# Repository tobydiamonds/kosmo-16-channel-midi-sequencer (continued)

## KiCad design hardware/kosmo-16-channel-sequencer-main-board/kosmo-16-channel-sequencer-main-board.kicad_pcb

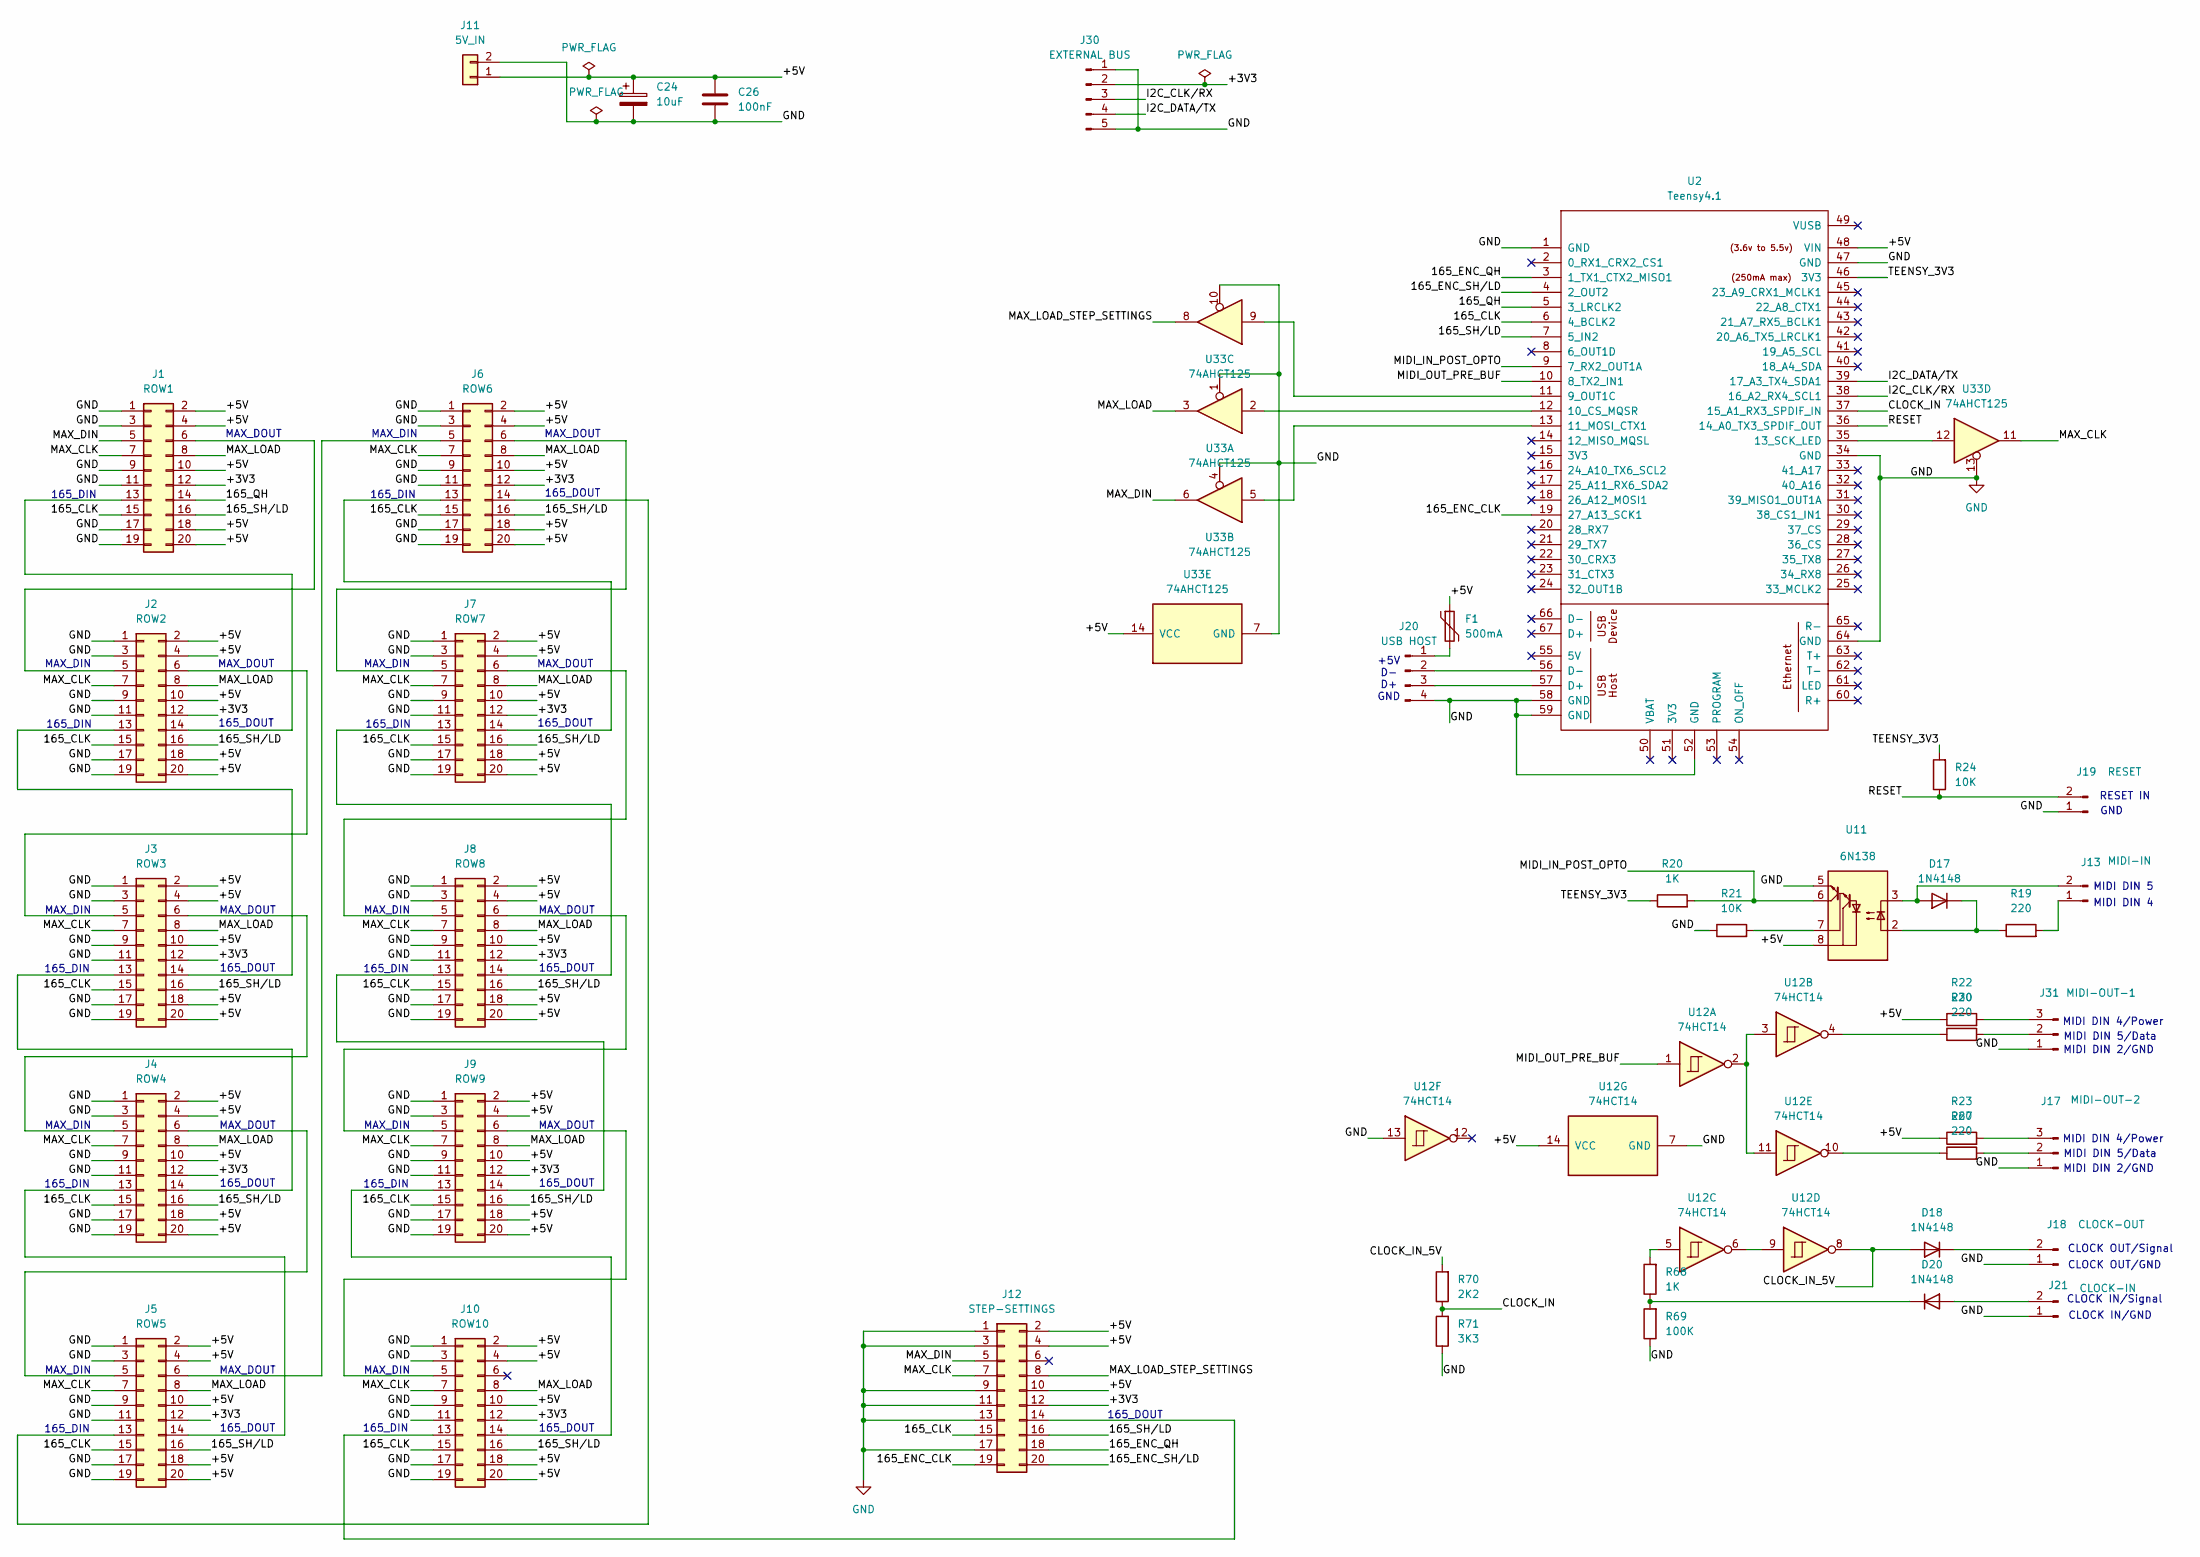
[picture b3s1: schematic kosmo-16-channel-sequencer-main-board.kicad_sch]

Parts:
C24: 10uF; CP_Radial_D6.3mm_P2.50mm
C26: 100nF; C_Disc_D5.0mm_W2.5mm_P5.00mm
D17, D18, D20: 1N4148; D_DO-35_SOD27_P7.62mm_Horizontal
F1: 500mA; Fuse_Bourns_MF-RHT050
J1: ROW1; PinHeader_2x10_P2.54mm_Vertical
J2: ROW2; PinHeader_2x10_P2.54mm_Vertical
J3: ROW3; PinHeader_2x10_P2.54mm_Vertical
J4: ROW4; PinHeader_2x10_P2.54mm_Vertical
J5: ROW5; PinHeader_2x10_P2.54mm_Vertical
J6: ROW6; PinHeader_2x10_P2.54mm_Vertical
J7: ROW7; PinHeader_2x10_P2.54mm_Vertical
J8: ROW8; PinHeader_2x10_P2.54mm_Vertical
J9: ROW9; PinHeader_2x10_P2.54mm_Vertical
J10: ROW10; PinHeader_2x10_P2.54mm_Vertical
J11: 5V_IN; TerminalBlock_Xinya_XY308-2.54-2P_1x02_P2.54mm_Horizontal
J12: STEP-SETTINGS; PinHeader_2x10_P2.54mm_Vertical
J13: MIDI-IN; PinHeader_1x02_P2.54mm_Vertical
J17: MIDI-OUT-2; PinHeader_1x03_P2.54mm_Vertical
J18: CLOCK-OUT; PinHeader_1x02_P2.54mm_Vertical
J19: RESET; PinHeader_1x02_P2.54mm_Vertical
J20: USB HOST; PinHeader_1x04_P2.54mm_Vertical
J21: CLOCK-IN; PinHeader_1x02_P2.54mm_Vertical
J30: EXTERNAL BUS; PinHeader_1x05_P2.54mm_Vertical
J31: MIDI-OUT-1; PinHeader_1x03_P2.54mm_Vertical
R19, R22, R23, R30, R67: 220; R_Axial_DIN0207_L6.3mm_D2.5mm_P7.62mm_Horizontal
R20, R68: 1K; R_Axial_DIN0207_L6.3mm_D2.5mm_P7.62mm_Horizontal
R21, R24: 10K; R_Axial_DIN0207_L6.3mm_D2.5mm_P7.62mm_Horizontal
R69: 100K; R_Axial_DIN0207_L6.3mm_D2.5mm_P7.62mm_Horizontal
R70: 2K2; R_Axial_DIN0207_L6.3mm_D2.5mm_P7.62mm_Horizontal
R71: 3K3; R_Axial_DIN0207_L6.3mm_D2.5mm_P7.62mm_Horizontal
U2: Teensy4.1; Teensy41
U11: 6N138; DIP-8_W7.62mm
U12: 74HCT14; DIP-14_W7.62mm
U33: 74AHCT125; DIP-14_W7.62mm

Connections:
/165_CLK: J1.15, J2.15, J3.15, J4.15, J5.15, J6.15, J7.15, J8.15, J9.15, J10.15, J12.15, U2.6 (4_BCLK2)
/165_ENC_CLK: J12.19, U2.19 (27_A13_SCK1)
/165_ENC_QH: J12.18, U2.3 (1_TX1_CTX2_MISO1)
/165_ENC_SH/LD: J12.20, U2.4 (2_OUT2)
/165_QH: J1.14, U2.5 (3_LRCLK2)
/165_SH/LD: J1.16, J2.16, J3.16, J4.16, J5.16, J6.16, J7.16, J8.16, J9.16, J10.16, J12.16, U2.7 (5_IN2)
/+3V3: J1.12, J2.12, J3.12, J4.12, J5.12, J6.12, J7.12, J8.12, J9.12, J10.12, J12.12, J30.2
/+5V: C24.1, C26.1, F1.1, J1.2, J1.4, J1.10, J1.18, J1.20, J2.2, J2.4, J2.10, J2.18, J2.20, J3.2, J3.4, J3.10, J3.18, J3.20, J4.2, J4.4, J4.10, J4.18, J4.20, J5.2, J5.4, J5.10, J5.18, J5.20, J6.2, J6.4, J6.10, J6.18, J6.20, J7.2, J7.4, J7.10, J7.18, J7.20, J8.2, J8.4, J8.10, J8.18, J8.20, J9.2, J9.4, J9.10, J9.18, J9.20, J10.2, J10.4, J10.10, J10.18, J10.20, J11.1, J12.2, J12.4, J12.10, R22.1, R23.1, U2.48 (VIN), U11.8 (VCC), U12.14 (VCC), U33.14 (VCC)
/CLOCK_IN: R70.1, R71.2, U2.37 (15_A1_RX3_SPDIF_IN)
/CLOCK_IN_5V: D18.2 (A), R70.2, U12.8
/I2C_CLK/RX: J30.3, U2.38 (16_A2_RX4_SCL1)
/I2C_DATA/TX: J30.4, U2.39 (17_A3_TX4_SDA1)
/MAX_CLK: J1.7, J2.7, J3.7, J4.7, J5.7, J6.7, J7.7, J8.7, J9.7, J10.7, J12.7, U33.11
/MAX_DIN: J1.5, J12.5, U33.6
/MAX_LOAD: J1.8, J2.8, J3.8, J4.8, J5.8, J6.8, J7.8, J8.8, J9.8, J10.8, U33.3
/MAX_LOAD_STEP_SETTINGS: J12.8, U33.8
/MIDI_IN_POST_OPTO: R20.2, U2.9 (7_RX2_OUT1A), U11.6 (VO2)
/MIDI_OUT_PRE_BUF: U2.10 (8_TX2_IN1), U12.1
/RESET: J19.2, R24.1, U2.36 (14_A0_TX3_SPDIF_OUT)
/TEENSY_3V3: R20.1, R24.2, U2.46 (3V3)
GND: C24.2, C26.2, J1.1, J1.3, J1.9, J1.11, J1.17, J1.19, J2.1, J2.3, J2.9, J2.11, J2.17, J2.19, J3.1, J3.3, J3.9, J3.11, J3.17, J3.19, J4.1, J4.3, J4.9, J4.11, J4.17, J4.19, J5.1, J5.3, J5.9, J5.11, J5.17, J5.19, J6.1, J6.3, J6.9, J6.11, J6.17, J6.19, J7.1, J7.3, J7.9, J7.11, J7.17, J7.19, J8.1, J8.3, J8.9, J8.11, J8.17, J8.19, J9.1, J9.3, J9.9, J9.11, J9.17, J9.19, J10.1, J10.3, J10.9, J10.11, J10.17, J10.19, J11.2, J12.1, J12.3, J12.9, J12.11, J12.13, J12.17, J17.1, J18.1, J19.1, J20.4, J21.1, J30.1, J30.5, J31.1, R21.1, R69.1, R71.1, U2.1 (GND), U2.34 (GND), U2.47 (GND), U2.52 (GND), U2.58 (GND), U2.59 (GND), U2.64 (GND), U11.5 (GND), U12.7 (GND), U12.13, U33.1, U33.4, U33.7 (GND), U33.10, U33.13
unnamed: D17.2 (A), J13.2, U11.3 (C2)
unnamed: D17.1 (K), R19.1, U11.2 (C1)
unnamed: D18.1 (K), J18.2
unnamed: D20.2 (A), J21.2
unnamed: D20.1 (K), R68.1, R69.2
unnamed: J1.6, J2.5
unnamed: J1.13, J2.14
unnamed: J2.6, J3.5
unnamed: J2.13, J3.14
unnamed: J3.6, J4.5
unnamed: J3.13, J4.14
unnamed: J4.6, J5.5
unnamed: J4.13, J5.14
unnamed: J5.6, J6.5
unnamed: J5.13, J6.14
unnamed: J6.6, J7.5
unnamed: J6.13, J7.14
unnamed: J7.6, J8.5
unnamed: J7.13, J8.14
unnamed: J8.6, J9.5
unnamed: J8.13, J9.14
unnamed: J9.6, J10.5
unnamed: J10.13, J12.14
unnamed: J9.13, J10.14
unnamed: J13.1, R19.2
unnamed: J17.2, R67.2
unnamed: J17.3, R23.2
unnamed: F1.2, J20.1
unnamed: J20.2, U2.56 (D-)
unnamed: J20.3, U2.57 (D+)
unnamed: J31.2, R30.2
unnamed: J31.3, R22.2
unnamed: R30.1, U12.4
unnamed: R67.1, U12.10
unnamed: R68.2, U12.5
unnamed: U2.11 (9_OUT1C), U33.9
unnamed: U2.12 (10_CS_MQSR), U33.2
unnamed: U2.13 (11_MOSI_CTX1), U33.5
unnamed: U2.35 (13_SCK_LED), U33.12
unnamed: R21.2, U11.7 (VO1)
unnamed: U12.6, U12.9
unnamed: U12.2, U12.3, U12.11

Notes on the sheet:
MAX_DIN
MAX_DOUT
MIDI DIN 2/GND
165_DOUT
165_DIN
MIDI DIN 4/Power
CLOCK IN/GND
MIDI DIN 5/Data
MIDI DIN 5
CLOCK OUT/GND
MIDI DIN 4
RESET IN
CLOCK OUT/Signal
+5V D- D+ GND
GND
CLOCK IN/Signal

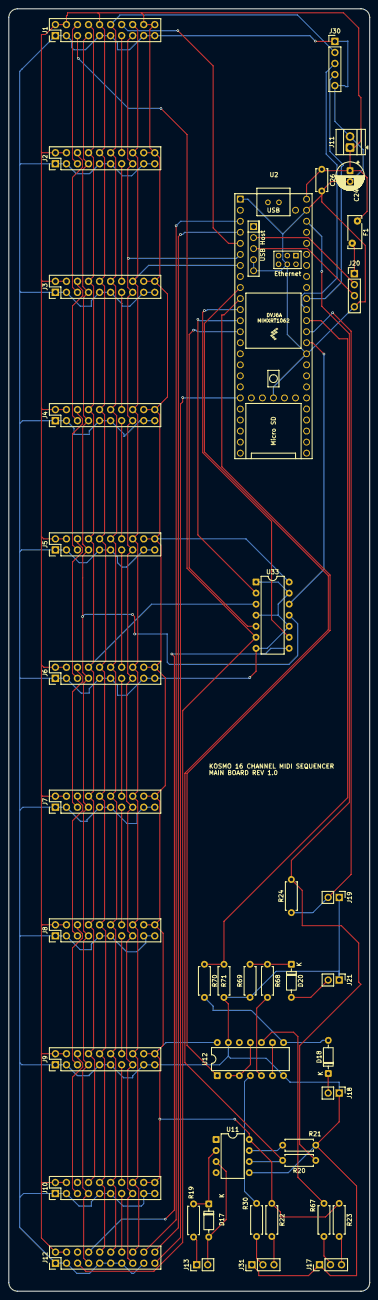
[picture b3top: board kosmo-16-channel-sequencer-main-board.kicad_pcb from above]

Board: 2 copper layers, 83.0 x 295.0 mm, 42 parts (0 on the bottom side), 63 nets.
